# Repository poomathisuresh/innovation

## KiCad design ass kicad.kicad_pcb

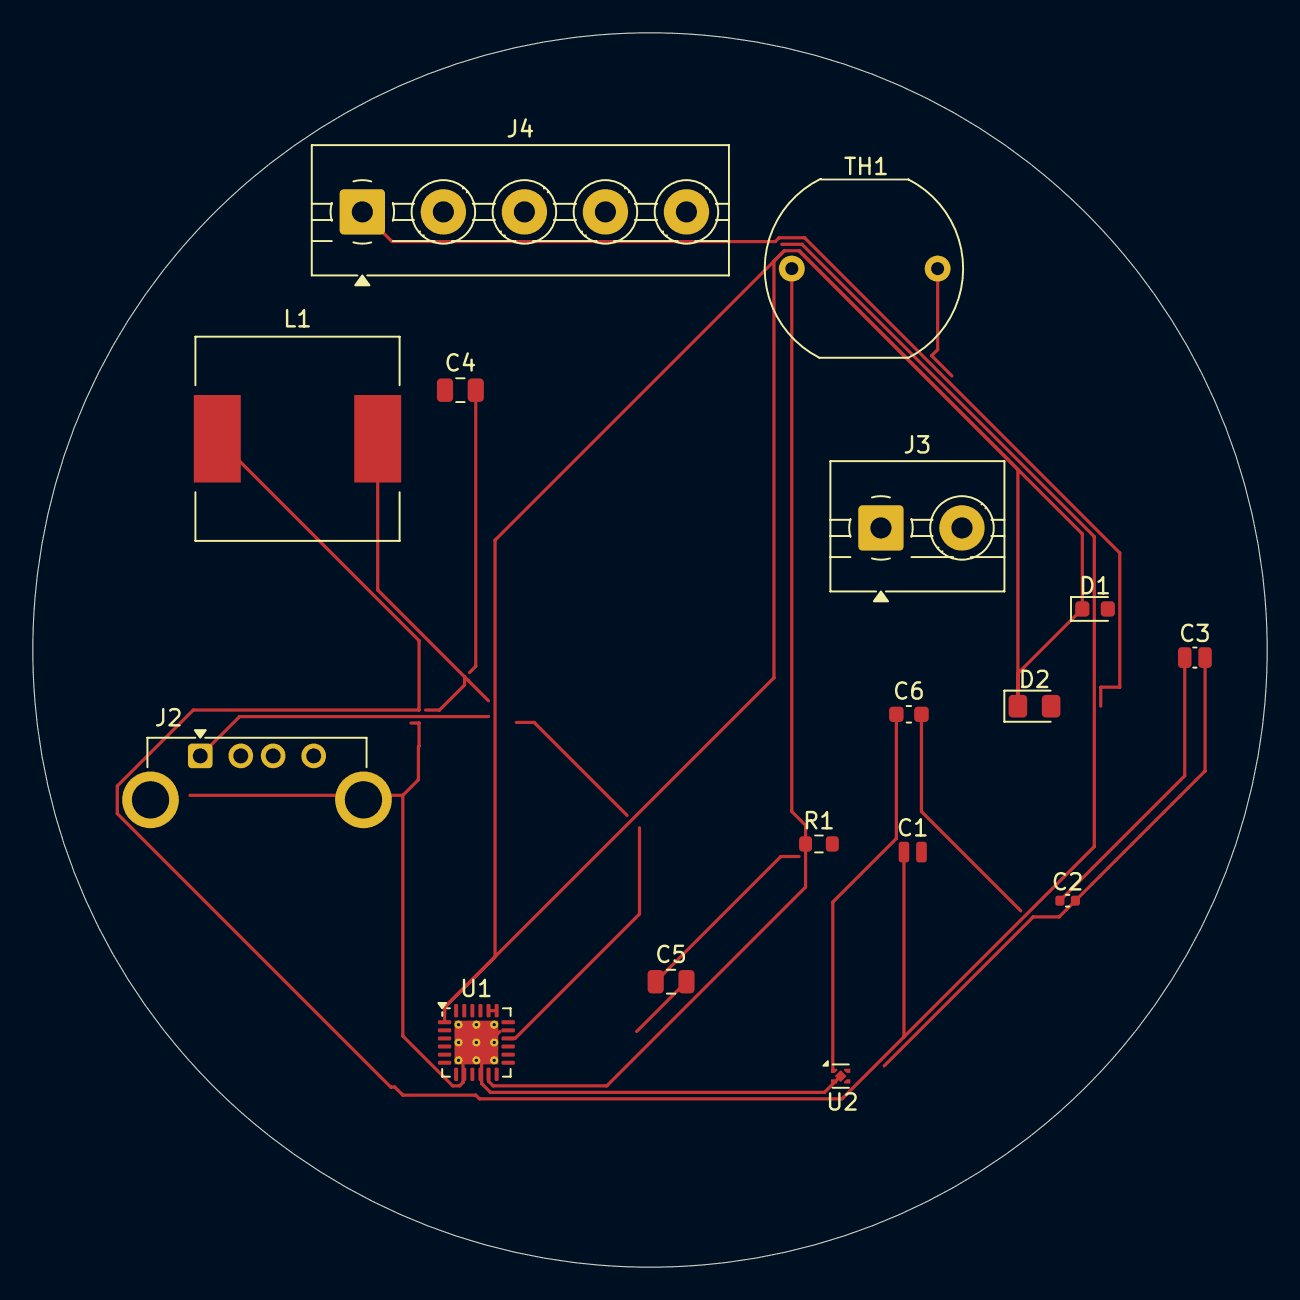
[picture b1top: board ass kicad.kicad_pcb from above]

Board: 2 copper layers, 76.2 x 76.2 mm, 16 parts (0 on the bottom side), 10 nets.

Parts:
C1: C; C_0504_1310Metric
C2: C; C_0402_1005Metric
C3: C; C_0504_1310Metric_Pad0.83x1.28mm_HandSolder
C4, C5: C; C_0805_2012Metric
C6: C; C_0603_1608Metric
D1: D; D_0603_1608Metric
D2: D; D_0805_2012Metric_Pad1.15x1.40mm_HandSolder
J2: USB_B_Micro; USB_A_Connfly_DS1095
J3: Screw_Terminal_01x01; TerminalBlock_MaiXu_MX126-5.0-02P_1x02_P5.00mm
J4: Screw_Terminal_01x01; TerminalBlock_MaiXu_MX126-5.0-05P_1x05_P5.00mm
L1: L; L_12x12mm_H8mm
R1: R; R_0603_1608Metric
TH1: Thermistor_NTC; R_LDR_12x10.8mm_P9.0mm_Vertical
U1: BQ25895RTW; Texas_RTW_WQFN-24-1EP_4x4mm_P0.5mm_EP2.7x2.7mm_ThermalVias
U2: NCP115AMX250TCG; OnSemi_XDFN4-1EP_1.0x1.0mm_EP0.52x0.52mm

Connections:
+3V3: C6.1, U2.1 (OUT)
GND: C2.2, C3.2, C4.2, C5.2, C6.2, J2.5 (GND), J3.1, TH1.2, U1.8 (OTG), U1.9 (~CE), U1.10 (ILIM), U1.17 (PGND), U1.18 (PGND), U1.25 (PGND), U2.2 (GND), U2.5 (GND)
unnamed: C1.1, L1.1, U1.19 (SW), U1.20 (SW)
unnamed: D1.2 (A), J2.1 (VBUS)
unnamed: D1.1 (K), D2.1 (K), U1.1 (VBUS)
unnamed: D2.2 (A), J4.1
unnamed: C1.2, U1.21 (BTST)
unnamed: C5.1, R1.2, U1.22 (REGN)
unnamed: R1.1, TH1.1, U1.11 (TS)
unnamed: C2.1, C3.1, C4.1, L1.2, U1.15 (SYS), U1.16 (SYS), U2.3 (EN), U2.4 (IN)

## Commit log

2025-04-02 design
